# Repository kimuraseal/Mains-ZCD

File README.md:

# Mains voltage (100V) Zero Cross Detector 
A Zero cross detector based on optocoupler.
The circuit outputs stable 10ms pulses on 50Hz AC and 8.334ms pulses on 60Hz AC systems.

# 商用電源電圧（100V）ゼロクロス検出器
フォトカプラを使用したゼロクロス検出回路。
本回路は、50Hz ACシステムでは安定した10msパルスを、60Hz ACシステムでは8.334msパルスを出力する。

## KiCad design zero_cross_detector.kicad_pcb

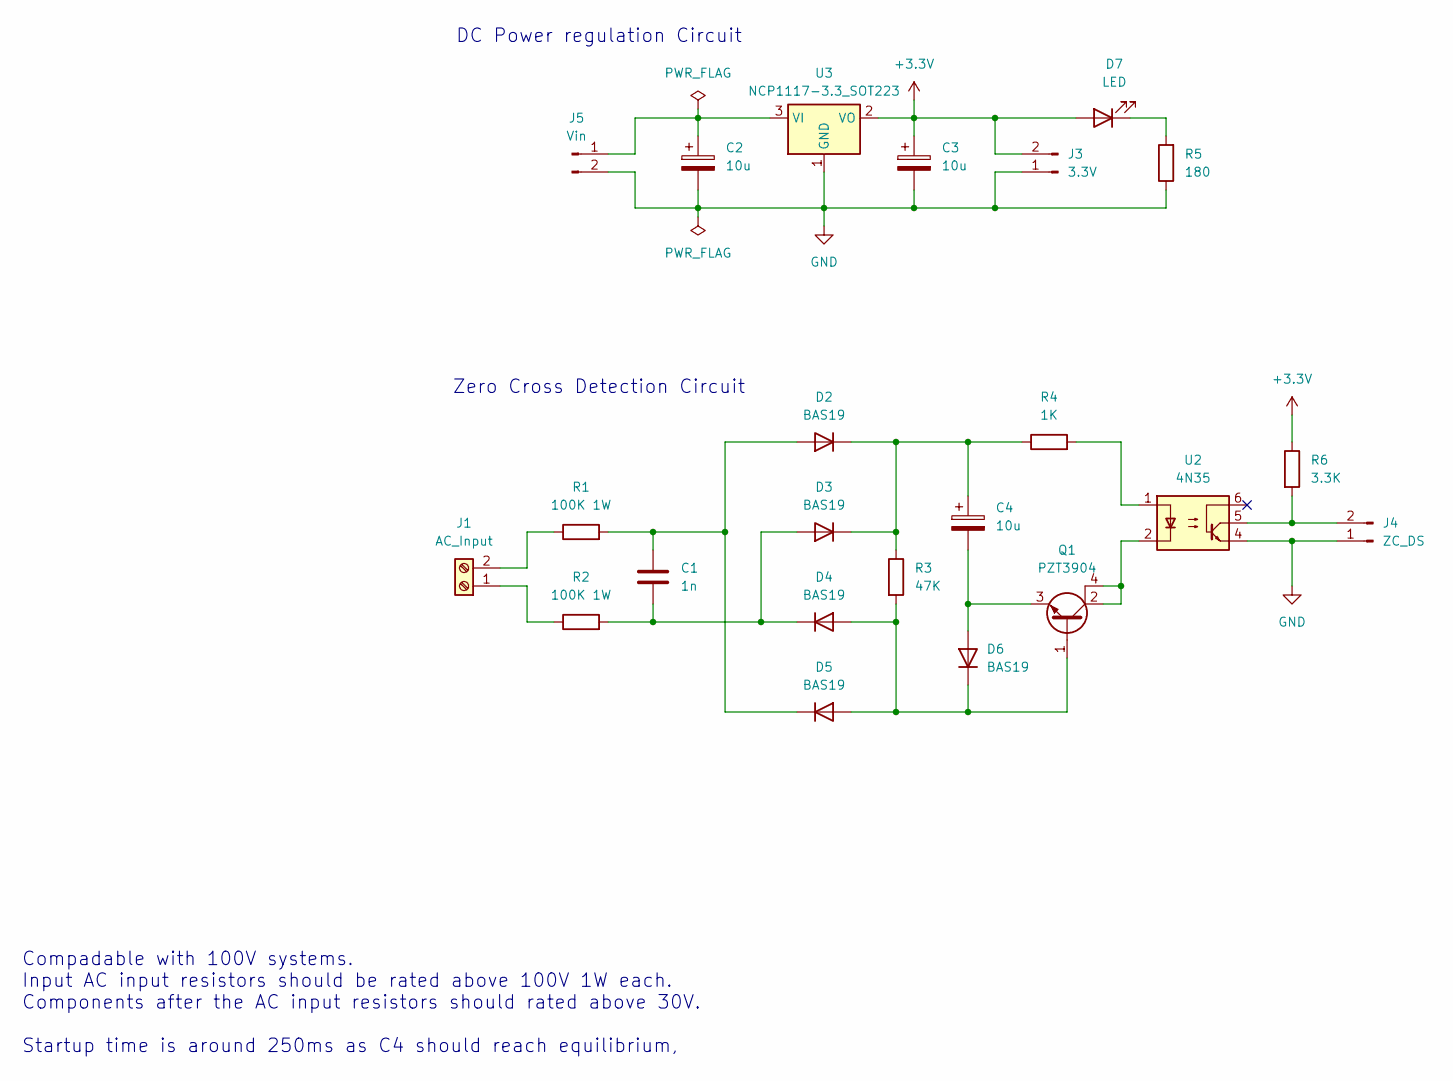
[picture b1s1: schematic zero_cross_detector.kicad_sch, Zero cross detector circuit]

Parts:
C1: 1n; C_0805_2012Metric_Pad1.18x1.45mm_HandSolder
C2, C3, C4: 10u; CP_Elec_6.3x4.9
D2, D3, D4, D5, D6: BAS19; SOT-23
D7: LED; LTST-C190GKT
J1: AC_Input; TerminalBlock_bornier-2_P5.08mm
J3: 3.3V; PinHeader_1x02_P2.54mm_Vertical
J4: ZC_DS; PinHeader_1x02_P2.54mm_Vertical
J5: Vin; PinHeader_1x02_P2.54mm_Vertical
Q1: PZT3904; SOT-223
R1, R2: 100K 1W; R_2512_6332Metric_Pad1.40x3.35mm_HandSolder
R3: 47K; R_0603_1608Metric_Pad0.98x0.95mm_HandSolder
R4: 1K; R_0603_1608Metric_Pad0.98x0.95mm_HandSolder
R5: 180; R_0603_1608Metric_Pad0.98x0.95mm_HandSolder
R6: 3.3K; R_0603_1608Metric_Pad0.98x0.95mm_HandSolder
U2: 4N35; DIP-6_W7.62mm
U3: NCP1117-3.3_SOT223; SOT-223-3_TabPin2

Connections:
+3.3V: C3.1, D7.2 (A), J3.2, R6.1, U3.2 (VO)
GND: C2.2, C3.2, J3.1, J4.1, J5.2, R5.1, U2.4, U3.1 (GND)
unnamed: C1.1, D2.1 (A), D5.3 (K), R1.2
unnamed: C4.1, D2.3 (K), D3.3 (K), R3.1, R4.1
unnamed: C1.2, D3.1 (A), D4.3 (K), R2.2
unnamed: D4.1 (A), D5.1 (A), D6.3 (K), Q1.1 (B), R3.2
unnamed: C4.2, D6.1 (A), Q1.3 (E)
unnamed: D7.1 (K), R5.2
unnamed: J1.1, R2.1
unnamed: J1.2, R1.1
unnamed: J4.2, R6.2, U2.5
unnamed: C2.1, J5.1, U3.3 (VI)
unnamed: Q1.2 (C), Q1.4 (C), U2.2
unnamed: R4.2, U2.1

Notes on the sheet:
Zero Cross Detection Circuit
DC Power regulation Circuit
Compadable with 100V systems. Input AC input resistors should be rated above 100V 1W each. Components after the AC input resistors should rated above 30V. Startup time is around 250ms as C4 should reach equilibrium,

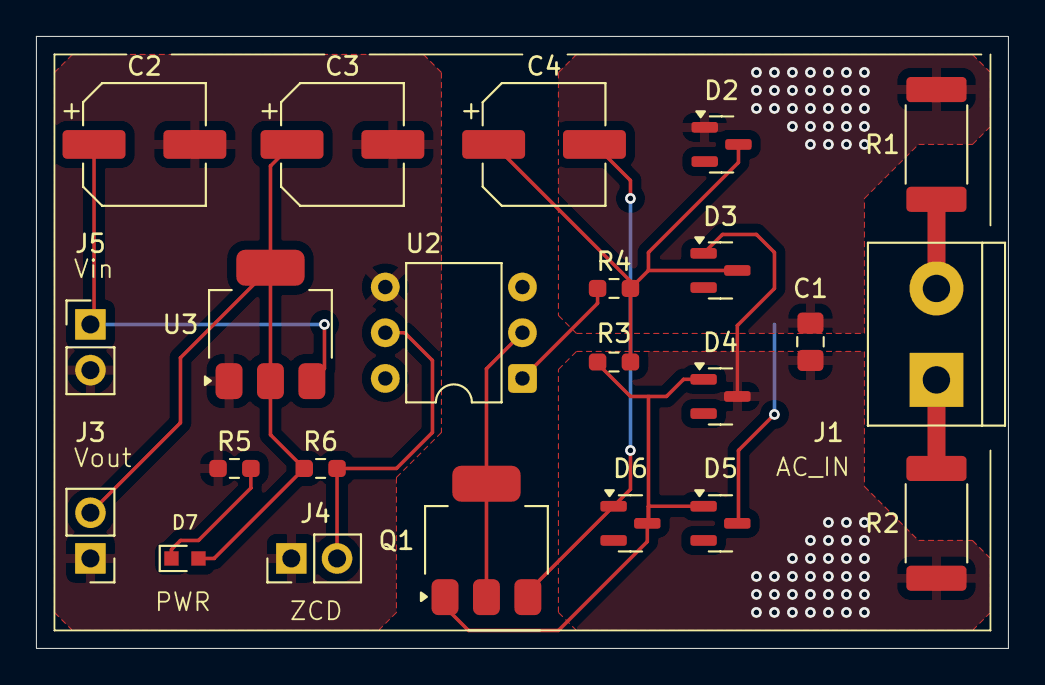
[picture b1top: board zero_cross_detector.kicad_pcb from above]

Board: 2 copper layers, 54.0 x 34.0 mm, 23 parts (0 on the bottom side), 14 nets.

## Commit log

2025-03-10 Init
2025-03-10 some changes to the schematic and added pdf schematic
2025-03-10 created sources.md
2025-03-10 BOM added
2025-03-10 updated pdf schematic
2025-03-11 PCB iteration one done
2025-03-11 some changes to the pcb
2025-03-11 Production Ready (before GERBER generation))
2025-03-11 Production ready
2025-03-11 auto changes by kicad
2025-03-11 folder restructure
2025-03-12 created improvements.md
2025-03-12 kicad backup
